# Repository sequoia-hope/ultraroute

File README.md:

# ultraroute

A KiCad autorouter under the MIT license, a benchmark that judges it by KiCad's own checks, and
**Studio**: a live, interactive view of the router at work. The project page is published at
<https://sequoia-hope.github.io/ultraroute/>; there the studio plays back recorded runs.

The router is the core in `core/`: Rust crates that read a `.kicad_pcb`, route it and write it
back, keeping every byte they did not change. It runs as a command, `ultraroute route`, and the
same code compiled to WebAssembly routes in the studio's browser tab. On the PCBench sample it
benchmarks on (200 boards, 120 s each), 164 boards come out clean by KiCad's DRC (see
`ROADMAP.md`, "State at 2026-10-30").

## Build and route a board

Needs Rust (`core/rust-toolchain.toml` pins 1.95.0). From `core/`:

```sh
cargo build --release -p ultraroute -p kicad-text
target/release/ultraroute route fixtures/earring.kicad_pcb -o /tmp/routed.kicad_pcb --timeout 120
```

With no stage named it runs the default recipe, the benchmark's. `kicad-text` (GPL, below) strokes
copper and mask text as KiCad does; without it text is a box round it, which can cover pads. The rules come from the
`.kicad_pro` and `.kicad_dru` beside the input; pours are left for KiCad to refill.
`core/README.md` lists the crates, the stages in their order, and every flag, and shows how to
judge the result with KiCad; `ultraroute route --help` prints the flags.
`docs/library.md` is for programs of your own built on the crates.

## Benchmark

`tools/pcbench.py` routes boards of [PCBench](https://github.com/emshotton/PCBench) from bare
pads and judges each by KiCad 9 (zone refill, then DRC). `docs/pcbench.md` says how to prepare
the boards, run a sample, and compare two runs against the noise floor.

## Run the studio

Needs Rust (with the `wasm32-unknown-unknown` target), `wasm-pack` and Node 22.

```sh
studio/build.sh
studio/target/release/studio-server --root . --port <port>
```

`build.sh` builds the server, the core's `ultraroute`, and the core as WebAssembly for the tab.
Then open `http://localhost:<port>/studio/`: pick a board, route it with the default recipe or
stages of your choice, watch it route, drag or nudge parts, lock them, and see where the board
is congested. On this machine the port comes from the project registry, and `./serve.sh` starts
the server.

A Boardroom project opens by its path: `/?project=<absolute path>&board=<name>&variant=<v>`
(board and variant may be left out when the project has one board). The studio routes
`hw/<board>/<variant>/<board>.kicad_pcb` with the `.kicad_pro`, `.kicad_dru` and `routing.json`
beside it; **Save to project** writes the routed board back over that file, unless it changed on
disk since it was loaded, and records the route and the router's report under
`apps.studio.<board>` in `design/status.json`.

| Path | What |
|---|---|
| `core/` | The router: crates, the `ultraroute` command, test fixtures |
| `studio/` | Server (runs the router, relays its live stream), Rust scene core compiled to WASM, Svelte client |
| `tools/pcbench.py`, `tools/lab.py` | The benchmark, and lab runs recorded under `~/Software/ultraroute-lab` |
| `docs/` | The library guide, the benchmark, the studio's design, research notes |
| `lab/` | Pages of recorded stage films and fan-out experiments |
| `ROADMAP.md` | The plan, phase by phase |

## Legacy: copperroute

Before the core, the router was [copperroute](https://github.com/sequoia-hope/copperroute) (branch
`governance`, forked from emshotton/copperroute), a Rust port of freerouting, run as a separate
program from a checkout at `copperroute/`. It is kept as a reference router. The studio can still
run it on the jobs that have a Specctra `.dsn` when its binary is at `target-
topo/release/copperroute` (or given with `--router PATH`); without it the studio routes on the core
alone. The tools of that era are kept under [`legacy/`](legacy/README.md): the leaderboard runner,
the two-router KiCad bench, the morph viewer and the experiment history. They are not maintained and
not on the Pages site. copperroute is GPL-3.0-only (a derivative of freerouting, with parts of
KiCad's design-rule checker); ultraroute does not include or link its code and runs it only as a
separate process.

## License

ultraroute is MIT-licensed; see [LICENSE](LICENSE). The core is our own code, written from the
file formats, so its WebAssembly build in the studio is MIT too. Code from GPL routers must stay
out of `core/` and `studio/`: linking it in, natively or as WebAssembly, would make the studio a
GPL work.

One crate is the exception, and it is a program, not a library: `core/crates/kicad-text` carries
KiCad's `newstroke` font and text layout, so it is GPL-3.0-or-later ([its LICENSE](core/crates/kicad-text/LICENSE)).
The reader runs it as a separate process (`kicad_pcb::text`), sending the board's texts on its
standard input and reading their strokes back; no MIT crate depends on it, which
`core/crates/kicad-pcb/tests/gpl_boundary.rs` checks over the whole dependency graph.

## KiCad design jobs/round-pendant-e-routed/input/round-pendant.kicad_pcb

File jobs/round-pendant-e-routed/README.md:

# round-pendant-e-routed

round-pendant's 8-layer variant E as released (github.com/sequoia-hope/round-pendant
`hw/round-pendant/e/round-pendant.*` at 2fcf971): a 38 mm round pendant, 235 XL-1010RGB LEDs on
a golden-angle spiral, five IS31FL3745 WLCSP-36 drivers, an RP2350A, 342 parts, 1218
connections, 5221 tracks and 879 vias. Every connection is joined: 0 DRC errors or warnings and
0 unconnected items by KiCad 9's DRC with `--severity-all`, as round-pendant reports.

It is a finished board to look at, not a routing job: the studio loads it as it is
(`strip: false`), and a route from it has nothing left to join. round-pendant routed it with
ultraroute in stages (`scripts/bga/critpass_d.py`, `escape_d.py`, `plough_finish_d.py`, then
`clean_copper_d.py`). One run from bare pads does not finish it yet: with its recipe
(`--strip --planes In2.Cu,In5.Cu --negotiate --rip-up --tighten --prefanout --prefanout-order inner
--prefanout-mode inner --diff-pairs --shove-plough region ... --cell 0.025`, 8 threads,
`--timeout 600`) the core at 24fb5d3 leaves 47 of 1042 connections open; with only `--strip` and
120 s, 104.

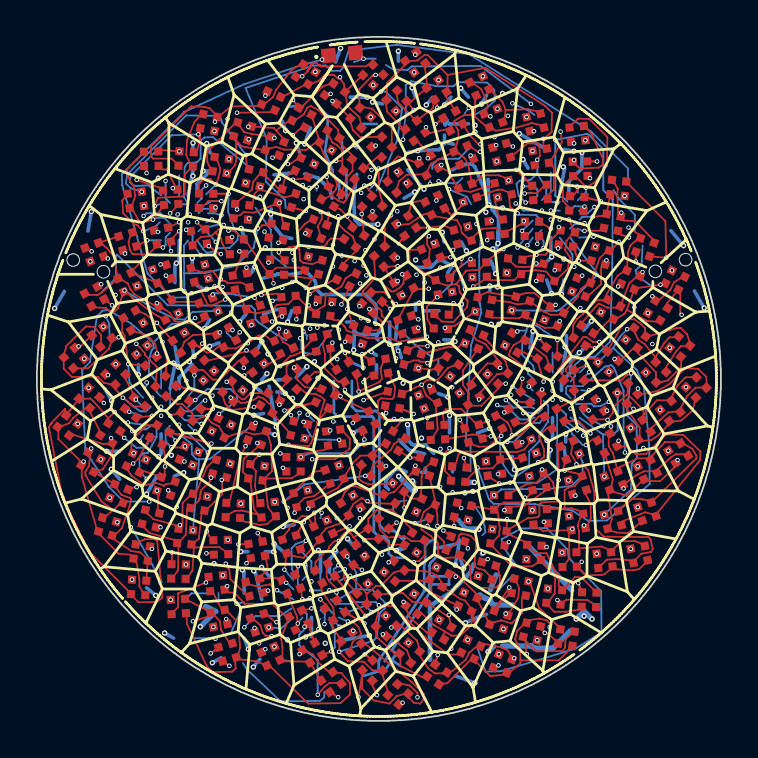
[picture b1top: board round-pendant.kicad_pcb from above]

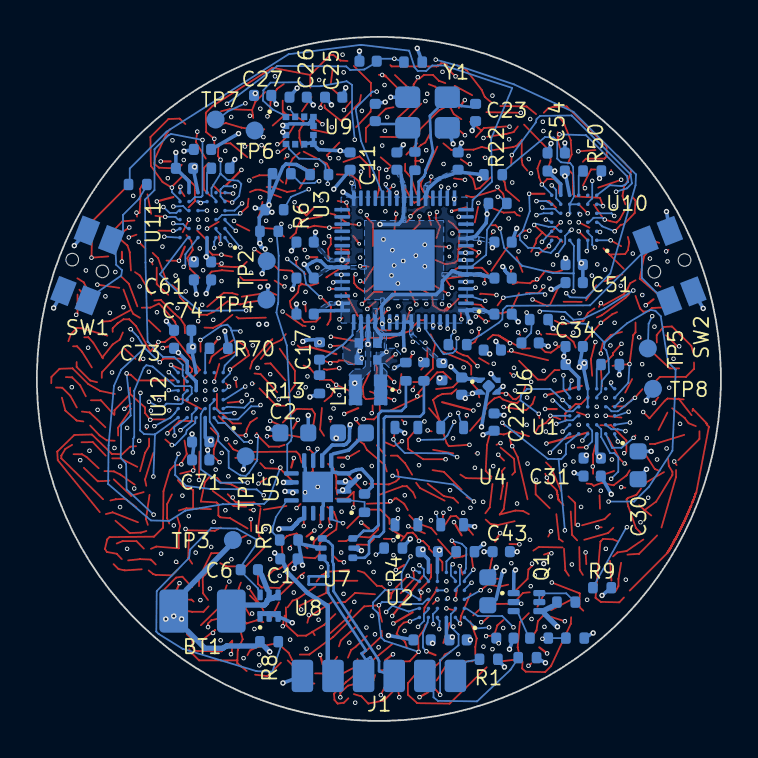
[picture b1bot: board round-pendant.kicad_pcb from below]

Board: 8 copper layers, 38.0 x 38.0 mm, 342 parts (106 on the bottom side), 185 nets.

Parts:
BT1: CELL 403535; BatteryPads
C1, C3, C4, C31, C34, C41, C44, C51, C54, C61, C64, C71, C74: 1u; C_0402_1005Metric
C2, C30, C40: 22u; C_0603_1608Metric
C5: 10u; C_0603_1608Metric
C6, C7, C8, C9, C10, C11, C12, C13, C14, C20, C21, C22, C25, C27, C32, C33, C35, C42, C43, C52, C53, C62, C63, C70, C72, C73: 100n; C_0402_1005Metric
C16, C18: 4.7u; C_0402_1005Metric_small_pads
C17, C19, C26: 4.7u; C_0402_1005Metric
C23, C24: 15p; C_0402_1005Metric
D1, D2, D3, D4, D5, D6, D7, D8, D9, D10, D11, D12, D13, D14, D15, D16, D17, D18, D19, D20, D21, D22, D23, D24, D25, D26, D27, D28, D29, D30, D31, D32, D33, D34, D35, D36, D37, D38, D39, D40, D41, D42, D43, D44, D45, D46, D47, D48, D49, D50, D51, D52, D53, D54, D55, D56, D57, D58, D59, D60, D61, D62, D63, D64, D65, D66, D67, D68, D69, D70, D71, D72, D73, D74, D75, D76, D77, D78, D79, D80, D81, D82, D83, D84, D85, D86, D87, D88, D89, D90, D91, D92, D93, D94, D95, D96, D97, D98, D99, D100, D101, D102, D103, D104, D105, D106, D107, D108, D109, D110, D111, D112, D113, D114, D115, D116, D117, D118, D119, D120, D121, D122, D123, D124, D125, D126, D127, D128, D129, D130, D131, D132, D133, D134, D135, D136, D137, D138, D139, D140, D141, D142, D143, D144, D145, D146, D147, D148, D149, D150, D151, D152, D153, D154, D155, D156, D157, D158, D159, D160, D161, D162, D163, D164, D165, D166, D167, D168, D169, D170, D171, D172, D173, D174, D175, D176, D177, D178, D179, D180, D181, D182, D183, D184, D185, D186, D187, D188, D189, D190, D191, D192, D193, D194, D195, D196, D197, D198, D199, D200, D201, D202, D203, D204, D205, D206, D207, D208, D209, D210, D211, D212, D213, D214, D215, D216, D217, D218, D219, D220, D221, D222, D223, D224, D225, D226, D227, D228, D229, D230, D231, D232, D233, D234, D235: RGB; LED_XL-1010RGB
J1: USB wires; USB_Pads
L1: 3.3u; L_pol_2016
Q1: NTZD3155C; SOT-563
Q2: ALS-PT19; SENSOR_ALS-PT19
R1, R2: 5.1k; R_0402_1005Metric
R3: 10k; R_0402_1005Metric
R4: 3k; R_0402_1005Metric
R5: 3.6k; R_0402_1005Metric
R6, R7, R9, R10, R11, R12, R31: 100k; R_0402_1005Metric
R8: 100R; R_0402_1005Metric
R13: 33R; R_0402_1005Metric
R14, R15: 27R; R_0402_1005Metric
R16, R17, R18, R21, R22: 1k; R_0402_1005Metric
R19, R20: 4.7k; R_0402_1005Metric
R30, R33, R50, R60, R70: 30k; R_0402_1005Metric
R43: 22k; R_0402_1005Metric
SW1: USER / WAKE; SW_Panasonic_EVQP7C
SW2: BOOTSEL; SW_Panasonic_EVQP7C
TP1: VSYS; TestPoint_Pad_D1.0mm
TP2: +3V3; TestPoint_Pad_D1.0mm
TP3: VBAT; TestPoint_Pad_D1.0mm
TP4: 1V1; TestPoint_Pad_D1.0mm
TP5: RUN; TestPoint_Pad_D1.0mm
TP6: SWCLK; TestPoint_Pad_D1.0mm
TP7: SWDIO; TestPoint_Pad_D1.0mm
TP8: GND; TestPoint_Pad_D1.0mm
U1, U2, U10, U11, U12: IS31FL3745; WLCSP-36_2.9x2.9mm_P0.5mm
U3: RP2350A; RP2350-QFN-60-1EP_7x7_P0.4mm_EP3.4x3.4mm_ThermalVias
U4: W25Q128JVPIQ; WSON-8_6x5mm_P1.27mm_NoEPCopper
U5: BQ24073; QFN-16-1EP_3x3mm_P0.5mm_EP1.7x1.7mm
U6: TPS7A0233; Texas_X2SON-4_1x1mm_P0.65mm
U7: USBLC6-2P6; SOT-666
U8: XB9901A; XySemi_DFN-6_1.8x1.4mm
U9: LIS2DW12; LGA-12_2x2mm_P0.5mm
Y1: 12MHz; Crystal_SMD_3225-4Pin_3.2x2.5mm

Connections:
+1V1: C18.1, C19.1, C20.1, C21.1, L1.1, TP4.1, U3.6, U3.23, U3.39, U3.50
+3V3: C4.1, C8.1, C9.1, C10.1, C11.1, C12.1, C13.1, C14.1, C16.1, C22.1, C25.1, C26.1, C27.1, R6.1, R7.1, R13.1, R19.1, R20.1, R21.1, R22.1, TP2.1, U3.1, U3.11, U3.20, U3.30, U3.38, U3.44, U3.45, U3.49, U3.53, U3.54, U4.8, U5.6, U6.1, U9.2, U9.3, U9.9, U9.10
/Driver 1 and matrix/CS1_1: D1.4, D2.4, D3.4, D4.4, D5.4, D6.4, D7.4, D8.4, U1.B2
/Driver 1 and matrix/CS1_2: D1.2, D2.2, D3.2, D4.2, D5.2, D6.2, D7.2, D8.2, U1.B3
/Driver 1 and matrix/CS1_3: D1.1, D2.1, D3.1, D4.1, D5.1, D6.1, D7.1, D8.1, U1.C3
/Driver 1 and matrix/CS1_4: D9.4, D10.4, D11.4, D12.4, D13.4, D14.4, D15.4, D16.4, U1.C2
/Driver 1 and matrix/CS1_5: D9.2, D10.2, D11.2, D12.2, D13.2, D14.2, D15.2, D16.2, U1.D2
/Driver 1 and matrix/CS1_6: D9.1, D10.1, D11.1, D12.1, D13.1, D14.1, D15.1, D16.1, U1.D1
/Driver 1 and matrix/CS1_7: D17.4, D18.4, D19.4, D20.4, D21.4, D22.4, D23.4, D24.4, U1.E2
/Driver 1 and matrix/CS1_8: D17.2, D18.2, D19.2, D20.2, D21.2, D22.2, D23.2, D24.2, U1.E1
/Driver 1 and matrix/CS1_9: D17.1, D18.1, D19.1, D20.1, D21.1, D22.1, D23.1, D24.1, U1.F1
/Driver 1 and matrix/CS1_10: D25.4, D26.4, D27.4, D28.4, D29.4, D30.4, D31.4, D32.4, U1.F6
/Driver 1 and matrix/CS1_11: D25.2, D26.2, D27.2, D28.2, D29.2, D30.2, D31.2, D32.2, U1.E6
/Driver 1 and matrix/CS1_12: D25.1, D26.1, D27.1, D28.1, D29.1, D30.1, D31.1, D32.1, U1.D5
/Driver 1 and matrix/CS1_13: D33.4, D34.4, D35.4, D36.4, D37.4, D38.4, D39.4, D40.4, U1.D6
/Driver 1 and matrix/CS1_14: D33.2, D34.2, D35.2, D36.2, D37.2, D38.2, D39.2, D40.2, U1.C4
/Driver 1 and matrix/CS1_15: D33.1, D34.1, D35.1, D36.1, D37.1, D38.1, D39.1, D40.1, U1.C6
/Driver 1 and matrix/CS1_16: D41.4, D42.4, D43.4, D44.4, D45.4, D46.4, D47.4, U1.C5
/Driver 1 and matrix/CS1_17: D41.2, D42.2, D43.2, D44.2, D45.2, D46.2, D47.2, U1.B4
/Driver 1 and matrix/CS1_18: D41.1, D42.1, D43.1, D44.1, D45.1, D46.1, D47.1, U1.B5
/Driver 1 and matrix/SW1_1: D1.3, D9.3, D17.3, D25.3, D33.3, D41.3, U1.A2
/Driver 1 and matrix/SW1_2: D2.3, D10.3, D18.3, D26.3, D34.3, D42.3, U1.A4
/Driver 1 and matrix/SW1_3: D3.3, D11.3, D19.3, D27.3, D35.3, D43.3, U1.A1
/Driver 1 and matrix/SW1_4: D4.3, D12.3, D20.3, D28.3, D36.3, D44.3, U1.A5
/Driver 1 and matrix/SW1_5: D5.3, D13.3, D21.3, D29.3, D37.3, D45.3, U1.B1
/Driver 1 and matrix/SW1_6: D6.3, D14.3, D22.3, D30.3, D38.3, D46.3, U1.A6
/Driver 1 and matrix/SW1_7: D7.3, D15.3, D23.3, D31.3, D39.3, D47.3, U1.C1
/Driver 1 and matrix/SW1_8: D8.3, D16.3, D24.3, D32.3, D40.3, U1.B6
/Driver 2 and matrix/CS2_1: D48.4, D49.4, D50.4, D51.4, D52.4, D53.4, D54.4, D55.4, U2.B2
/Driver 2 and matrix/CS2_2: D48.2, D49.2, D50.2, D51.2, D52.2, D53.2, D54.2, D55.2, U2.B3
/Driver 2 and matrix/CS2_3: D48.1, D49.1, D50.1, D51.1, D52.1, D53.1, D54.1, D55.1, U2.C3
/Driver 2 and matrix/CS2_4: D56.4, D57.4, D58.4, D59.4, D60.4, D61.4, D62.4, D63.4, U2.C2
/Driver 2 and matrix/CS2_5: D56.2, D57.2, D58.2, D59.2, D60.2, D61.2, D62.2, D63.2, U2.D2
/Driver 2 and matrix/CS2_6: D56.1, D57.1, D58.1, D59.1, D60.1, D61.1, D62.1, D63.1, U2.D1
/Driver 2 and matrix/CS2_7: D64.4, D65.4, D66.4, D67.4, D68.4, D69.4, D70.4, D71.4, U2.E2
/Driver 2 and matrix/CS2_8: D64.2, D65.2, D66.2, D67.2, D68.2, D69.2, D70.2, D71.2, U2.E1
/Driver 2 and matrix/CS2_9: D64.1, D65.1, D66.1, D67.1, D68.1, D69.1, D70.1, D71.1, U2.F1
/Driver 2 and matrix/CS2_10: D72.4, D73.4, D74.4, D75.4, D76.4, D77.4, D78.4, D79.4, U2.F6
/Driver 2 and matrix/CS2_11: D72.2, D73.2, D74.2, D75.2, D76.2, D77.2, D78.2, D79.2, U2.E6
/Driver 2 and matrix/CS2_12: D72.1, D73.1, D74.1, D75.1, D76.1, D77.1, D78.1, D79.1, U2.D5
/Driver 2 and matrix/CS2_13: D80.4, D81.4, D82.4, D83.4, D84.4, D85.4, D86.4, D87.4, U2.D6
/Driver 2 and matrix/CS2_14: D80.2, D81.2, D82.2, D83.2, D84.2, D85.2, D86.2, D87.2, U2.C4
/Driver 2 and matrix/CS2_15: D80.1, D81.1, D82.1, D83.1, D84.1, D85.1, D86.1, D87.1, U2.C6
/Driver 2 and matrix/CS2_16: D88.4, D89.4, D90.4, D91.4, D92.4, D93.4, D94.4, U2.C5
/Driver 2 and matrix/CS2_17: D88.2, D89.2, D90.2, D91.2, D92.2, D93.2, D94.2, U2.B4
/Driver 2 and matrix/CS2_18: D88.1, D89.1, D90.1, D91.1, D92.1, D93.1, D94.1, U2.B5
/Driver 2 and matrix/SW2_1: D48.3, D56.3, D64.3, D72.3, D80.3, D88.3, U2.A2
/Driver 2 and matrix/SW2_2: D49.3, D57.3, D65.3, D73.3, D81.3, D89.3, U2.A4
/Driver 2 and matrix/SW2_3: D50.3, D58.3, D66.3, D74.3, D82.3, D90.3, U2.A1
/Driver 2 and matrix/SW2_4: D51.3, D59.3, D67.3, D75.3, D83.3, D91.3, U2.A5
/Driver 2 and matrix/SW2_5: D52.3, D60.3, D68.3, D76.3, D84.3, D92.3, U2.B1
/Driver 2 and matrix/SW2_6: D53.3, D61.3, D69.3, D77.3, D85.3, D93.3, U2.A6
/Driver 2 and matrix/SW2_7: D54.3, D62.3, D70.3, D78.3, D86.3, D94.3, U2.C1
/Driver 2 and matrix/SW2_8: D55.3, D63.3, D71.3, D79.3, D87.3, U2.B6
/Driver 3 and matrix/CS3_1: D95.4, D96.4, D97.4, D98.4, D99.4, D100.4, D101.4, D102.4, U10.B2
/Driver 3 and matrix/CS3_2: D95.2, D96.2, D97.2, D98.2, D99.2, D100.2, D101.2, D102.2, U10.B3
/Driver 3 and matrix/CS3_3: D95.1, D96.1, D97.1, D98.1, D99.1, D100.1, D101.1, D102.1, U10.C3
/Driver 3 and matrix/CS3_4: D103.4, D104.4, D105.4, D106.4, D107.4, D108.4, D109.4, D110.4, U10.C2
/Driver 3 and matrix/CS3_5: D103.2, D104.2, D105.2, D106.2, D107.2, D108.2, D109.2, D110.2, U10.D2
/Driver 3 and matrix/CS3_6: D103.1, D104.1, D105.1, D106.1, D107.1, D108.1, D109.1, D110.1, U10.D1
/Driver 3 and matrix/CS3_7: D111.4, D112.4, D113.4, D114.4, D115.4, D116.4, D117.4, D118.4, U10.E2
/Driver 3 and matrix/CS3_8: D111.2, D112.2, D113.2, D114.2, D115.2, D116.2, D117.2, D118.2, U10.E1
/Driver 3 and matrix/CS3_9: D111.1, D112.1, D113.1, D114.1, D115.1, D116.1, D117.1, D118.1, U10.F1
/Driver 3 and matrix/CS3_10: D119.4, D120.4, D121.4, D122.4, D123.4, D124.4, D125.4, D126.4, U10.F6
/Driver 3 and matrix/CS3_11: D119.2, D120.2, D121.2, D122.2, D123.2, D124.2, D125.2, D126.2, U10.E6
/Driver 3 and matrix/CS3_12: D119.1, D120.1, D121.1, D122.1, D123.1, D124.1, D125.1, D126.1, U10.D5
/Driver 3 and matrix/CS3_13: D127.4, D128.4, D129.4, D130.4, D131.4, D132.4, D133.4, D134.4, U10.D6
/Driver 3 and matrix/CS3_14: D127.2, D128.2, D129.2, D130.2, D131.2, D132.2, D133.2, D134.2, U10.C4
/Driver 3 and matrix/CS3_15: D127.1, D128.1, D129.1, D130.1, D131.1, D132.1, D133.1, D134.1, U10.C6
/Driver 3 and matrix/CS3_16: D135.4, D136.4, D137.4, D138.4, D139.4, D140.4, D141.4, U10.C5
/Driver 3 and matrix/CS3_17: D135.2, D136.2, D137.2, D138.2, D139.2, D140.2, D141.2, U10.B4
/Driver 3 and matrix/CS3_18: D135.1, D136.1, D137.1, D138.1, D139.1, D140.1, D141.1, U10.B5
/Driver 3 and matrix/SW3_1: D95.3, D103.3, D111.3, D119.3, D127.3, D135.3, U10.A2
/Driver 3 and matrix/SW3_2: D96.3, D104.3, D112.3, D120.3, D128.3, D136.3, U10.A4
/Driver 3 and matrix/SW3_3: D97.3, D105.3, D113.3, D121.3, D129.3, D137.3, U10.A1
/Driver 3 and matrix/SW3_4: D98.3, D106.3, D114.3, D122.3, D130.3, D138.3, U10.A5
/Driver 3 and matrix/SW3_5: D99.3, D107.3, D115.3, D123.3, D131.3, D139.3, U10.B1
/Driver 3 and matrix/SW3_6: D100.3, D108.3, D116.3, D124.3, D132.3, D140.3, U10.A6
/Driver 3 and matrix/SW3_7: D101.3, D109.3, D117.3, D125.3, D133.3, D141.3, U10.C1
/Driver 3 and matrix/SW3_8: D102.3, D110.3, D118.3, D126.3, D134.3, U10.B6
/Driver 4 and matrix/CS4_1: D142.4, D143.4, D144.4, D145.4, D146.4, D147.4, D148.4, D149.4, U11.B2
/Driver 4 and matrix/CS4_2: D142.2, D143.2, D144.2, D145.2, D146.2, D147.2, D148.2, D149.2, U11.B3
/Driver 4 and matrix/CS4_3: D142.1, D143.1, D144.1, D145.1, D146.1, D147.1, D148.1, D149.1, U11.C3
/Driver 4 and matrix/CS4_4: D150.4, D151.4, D152.4, D153.4, D154.4, D155.4, D156.4, D157.4, U11.C2
/Driver 4 and matrix/CS4_5: D150.2, D151.2, D152.2, D153.2, D154.2, D155.2, D156.2, D157.2, U11.D2
/Driver 4 and matrix/CS4_6: D150.1, D151.1, D152.1, D153.1, D154.1, D155.1, D156.1, D157.1, U11.D1
/Driver 4 and matrix/CS4_7: D158.4, D159.4, D160.4, D161.4, D162.4, D163.4, D164.4, D165.4, U11.E2
/Driver 4 and matrix/CS4_8: D158.2, D159.2, D160.2, D161.2, D162.2, D163.2, D164.2, D165.2, U11.E1
/Driver 4 and matrix/CS4_9: D158.1, D159.1, D160.1, D161.1, D162.1, D163.1, D164.1, D165.1, U11.F1
/Driver 4 and matrix/CS4_10: D166.4, D167.4, D168.4, D169.4, D170.4, D171.4, D172.4, D173.4, U11.F6
/Driver 4 and matrix/CS4_11: D166.2, D167.2, D168.2, D169.2, D170.2, D171.2, D172.2, D173.2, U11.E6
/Driver 4 and matrix/CS4_12: D166.1, D167.1, D168.1, D169.1, D170.1, D171.1, D172.1, D173.1, U11.D5
/Driver 4 and matrix/CS4_13: D174.4, D175.4, D176.4, D177.4, D178.4, D179.4, D180.4, D181.4, U11.D6
/Driver 4 and matrix/CS4_14: D174.2, D175.2, D176.2, D177.2, D178.2, D179.2, D180.2, D181.2, U11.C4
/Driver 4 and matrix/CS4_15: D174.1, D175.1, D176.1, D177.1, D178.1, D179.1, D180.1, D181.1, U11.C6
/Driver 4 and matrix/CS4_16: D182.4, D183.4, D184.4, D185.4, D186.4, D187.4, D188.4, U11.C5
/Driver 4 and matrix/CS4_17: D182.2, D183.2, D184.2, D185.2, D186.2, D187.2, D188.2, U11.B4
/Driver 4 and matrix/CS4_18: D182.1, D183.1, D184.1, D185.1, D186.1, D187.1, D188.1, U11.B5
/Driver 4 and matrix/SW4_1: D142.3, D150.3, D158.3, D166.3, D174.3, D182.3, U11.A2
/Driver 4 and matrix/SW4_2: D143.3, D151.3, D159.3, D167.3, D175.3, D183.3, U11.A4
/Driver 4 and matrix/SW4_3: D144.3, D152.3, D160.3, D168.3, D176.3, D184.3, U11.A1
/Driver 4 and matrix/SW4_4: D145.3, D153.3, D161.3, D169.3, D177.3, D185.3, U11.A5
/Driver 4 and matrix/SW4_5: D146.3, D154.3, D162.3, D170.3, D178.3, D186.3, U11.B1
/Driver 4 and matrix/SW4_6: D147.3, D155.3, D163.3, D171.3, D179.3, D187.3, U11.A6
/Driver 4 and matrix/SW4_7: D148.3, D156.3, D164.3, D172.3, D180.3, D188.3, U11.C1
/Driver 4 and matrix/SW4_8: D149.3, D157.3, D165.3, D173.3, D181.3, U11.B6
/Driver 5 and matrix/CS5_1: D189.4, D190.4, D191.4, D192.4, D193.4, D194.4, D195.4, D196.4, U12.B2
/Driver 5 and matrix/CS5_2: D189.2, D190.2, D191.2, D192.2, D193.2, D194.2, D195.2, D196.2, U12.B3
/Driver 5 and matrix/CS5_3: D189.1, D190.1, D191.1, D192.1, D193.1, D194.1, D195.1, D196.1, U12.C3
/Driver 5 and matrix/CS5_4: D197.4, D198.4, D199.4, D200.4, D201.4, D202.4, D203.4, D204.4, U12.C2
/Driver 5 and matrix/CS5_5: D197.2, D198.2, D199.2, D200.2, D201.2, D202.2, D203.2, D204.2, U12.D2
/Driver 5 and matrix/CS5_6: D197.1, D198.1, D199.1, D200.1, D201.1, D202.1, D203.1, D204.1, U12.D1
/Driver 5 and matrix/CS5_7: D205.4, D206.4, D207.4, D208.4, D209.4, D210.4, D211.4, D212.4, U12.E2
/Driver 5 and matrix/CS5_8: D205.2, D206.2, D207.2, D208.2, D209.2, D210.2, D211.2, D212.2, U12.E1
/Driver 5 and matrix/CS5_9: D205.1, D206.1, D207.1, D208.1, D209.1, D210.1, D211.1, D212.1, U12.F1
/Driver 5 and matrix/CS5_10: D213.4, D214.4, D215.4, D216.4, D217.4, D218.4, D219.4, D220.4, U12.F6
/Driver 5 and matrix/CS5_11: D213.2, D214.2, D215.2, D216.2, D217.2, D218.2, D219.2, D220.2, U12.E6
/Driver 5 and matrix/CS5_12: D213.1, D214.1, D215.1, D216.1, D217.1, D218.1, D219.1, D220.1, U12.D5
/Driver 5 and matrix/CS5_13: D221.4, D222.4, D223.4, D224.4, D225.4, D226.4, D227.4, D228.4, U12.D6
/Driver 5 and matrix/CS5_14: D221.2, D222.2, D223.2, D224.2, D225.2, D226.2, D227.2, D228.2, U12.C4
/Driver 5 and matrix/CS5_15: D221.1, D222.1, D223.1, D224.1, D225.1, D226.1, D227.1, D228.1, U12.C6
/Driver 5 and matrix/CS5_16: D229.4, D230.4, D231.4, D232.4, D233.4, D234.4, D235.4, U12.C5
/Driver 5 and matrix/CS5_17: D229.2, D230.2, D231.2, D232.2, D233.2, D234.2, D235.2, U12.B4
/Driver 5 and matrix/CS5_18: D229.1, D230.1, D231.1, D232.1, D233.1, D234.1, D235.1, U12.B5
/Driver 5 and matrix/SW5_1: D189.3, D197.3, D205.3, D213.3, D221.3, D229.3, U12.A2
/Driver 5 and matrix/SW5_2: D190.3, D198.3, D206.3, D214.3, D222.3, D230.3, U12.A4
/Driver 5 and matrix/SW5_3: D191.3, D199.3, D207.3, D215.3, D223.3, D231.3, U12.A1
/Driver 5 and matrix/SW5_4: D192.3, D200.3, D208.3, D216.3, D224.3, D232.3, U12.A5
/Driver 5 and matrix/SW5_5: D193.3, D201.3, D209.3, D217.3, D225.3, D233.3, U12.B1
/Driver 5 and matrix/SW5_6: D194.3, D202.3, D210.3, D218.3, D226.3, D234.3, U12.A6
/Driver 5 and matrix/SW5_7: D195.3, D203.3, D211.3, D219.3, D227.3, D235.3, U12.C1
/Driver 5 and matrix/SW5_8: D196.3, D204.3, D212.3, D220.3, D228.3, U12.B6
/MCU/ACC_INT: U3.14, U9.12
/MCU/ACC_SCL: R19.2, U3.5, U9.1
/MCU/ACC_SDA: R20.2, U3.4, U9.4
/MCU/BTN: R18.1, U3.15
/MCU/LIGHT: C70.1, Q2.2, R43.1, U3.41
/MCU/LIGHT_PWR: Q2.1, U3.3
/MCU/QSPI_SCLK: U3.56, U4.6
/MCU/QSPI_SD0: U3.57, U4.5
/MCU/QSPI_SD1: U3.59, U4.2
/MCU/QSPI_SD2: U3.58, U4.3
/MCU/QSPI_SD3: U3.55, U4.7
/MCU/QSPI_SS: R16.1, U3.60, U4.1
/MCU/RUN: TP5.1, U3.26
/MCU/SWCLK: TP6.1, U3.24
/MCU/SWDIO: TP7.1, U3.25
/MCU/USB_DM_MCU: R14.2, U3.51
/MCU/USB_DP_MCU: R15.2, U3.52
/MCU/VREG_AVDD: C17.1, R13.2, U3.46
/MCU/VREG_LX: L1.2, U3.48
/Power/BAT_N: BT1.2, C6.2, U8.4, U8.5
/Power/CC1: J1.1, R1.1
/Power/CC2: J1.2, R2.1
/Power/USB_DM_C: J1.3, U7.1
/Power/USB_DP_C: J1.4, U7.3
CHG: R7.2, U3.16, U5.9
GND: C1.2, C2.2, C3.2, C4.2, C5.2, C7.2, C8.2, C9.2, C10.2, C11.2, C12.2, C13.2, C14.2, C16.2, C17.2, C18.2, C19.2, C20.2, C21.2, C22.2, C23.2, C24.2, C25.2, C26.2, C27.2, C30.2, C31.2, C32.2, C33.2, C34.2, C35.2, C40.2, C41.2, C42.2, C43.2, C44.2, C51.2, C52.2, C53.2, C54.2, C61.2, C62.2, C63.2, C64.2, C70.2, C71.2, C72.2, C73.2, C74.2, J1.6, Q1.1, R1.2, R2.2, R3.2, R4.2, R5.2, R9.2, R12.2, R30.2, R31.2, R33.2, R43.2, R50.2, R60.2, R70.2, SW1.2, SW2.2, TP8.1, U1.D4, U1.E4, U1.F4, U2.E4, U2.F4, U3.47, U3.61, U4.4, U5.4, U5.5, U5.8, U5.15, U5.17, U6.2, U6.5, U7.2, U8.1, U8.2, U8.3, U9.6, U9.7, U9.8, U10.F4, U11.F4, U12.F4, Y1.2, Y1.4
I2C_SCL: R22.2, U1.E3, U2.E3, U3.8, U10.D4, U10.E3, U10.E4, U11.E3, U11.E4, U12.E3
I2C_SDA: R21.2, U1.D3, U2.D3, U2.D4, U3.7, U10.D3, U11.D3, U11.D4, U12.D3
LED_SDB: C35.1, R31.1, U1.E5, U2.E5, U3.9, U10.E5, U11.E5, U12.E5
unnamed: C24.1, R17.1, Y1.3
unnamed: Q1.5, Q1.6, R10.2
unnamed: Q1.3, R11.1
unnamed: R16.2, SW2.1
unnamed: R18.2, SW1.1
unnamed: R30.1, U1.F3
unnamed: R33.1, U2.F3
unnamed: C23.1, U3.21, Y1.1
unnamed: R17.2, U3.22
unnamed: R5.1, U5.12
unnamed: R4.1, U5.16
unnamed: R3.1, U5.1
unnamed: C6.1, R8.2, U8.6
unnamed: R50.1, U10.F3
unnamed: R60.1, U11.F3
unnamed: R70.1, U12.F3
PGOOD: R6.2, U3.17, U5.7
USB_DM: R14.1, U7.6
USB_DP: R15.1, U7.4
VBAT: BT1.1, C5.1, Q1.4, R8.1, R10.1, TP3.1, U5.2, U5.3
VBAT_EN: Q1.2, R9.1, U3.18
VBAT_SENSE: C7.1, R11.2, R12.1, U3.40
VBUS: C1.1, J1.5, U5.13, U7.5
VSYS: C2.1, C3.1, C30.1, C31.1, C32.1, C33.1, C34.1, C40.1, C41.1, C42.1, C43.1, C44.1, C51.1, C52.1, C53.1, C54.1, C61.1, C62.1, C63.1, C64.1, C71.1, C72.1, C73.1, C74.1, TP1.1, U1.A3, U1.F5, U2.A3, U2.F5, U5.10, U5.11, U6.3, U6.4, U10.A3, U10.F5, U11.A3, U11.F5, U12.A3, U12.D4, U12.E4, U12.F5

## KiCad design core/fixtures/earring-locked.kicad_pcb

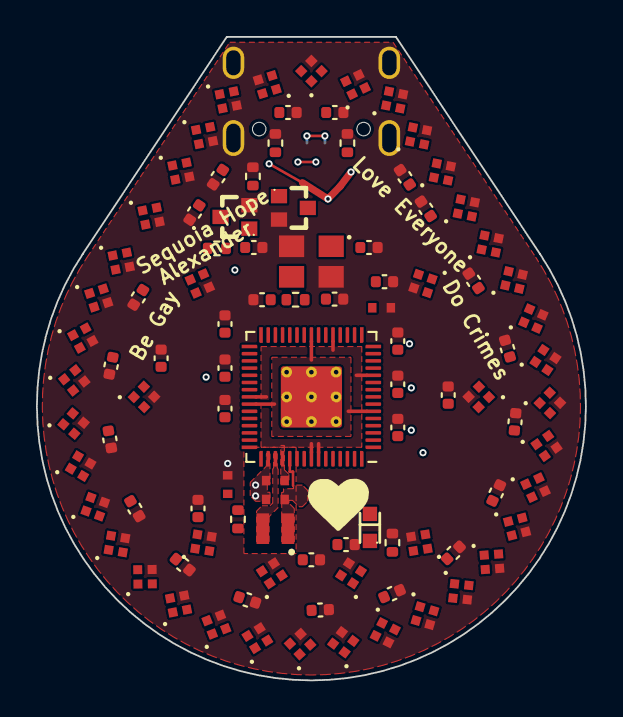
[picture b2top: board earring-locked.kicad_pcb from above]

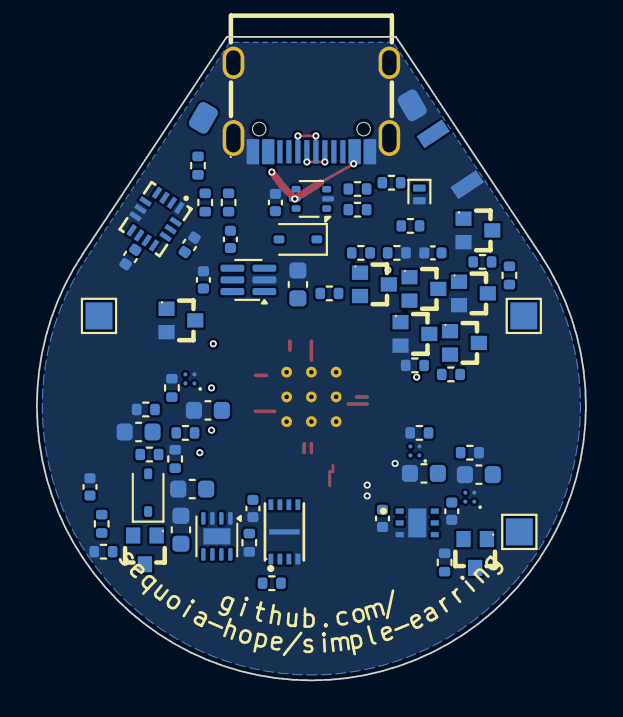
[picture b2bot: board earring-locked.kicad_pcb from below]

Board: 4 copper layers, 30.5 x 35.8 mm, 167 parts (70 on the bottom side), 103 nets.

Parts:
BT1: LPR302823; BAT_LPR302823_PADS
C1, C2, C3, C4, C5, C6, C7, C8, C9, C21, C23, C24, C25, C26, C27, C28, C30, C32, C34, C36, C38, C40, C42, C44, C46, C48, C50, C52, C54, C56, C58, C60, C62, C64, C66, C68, C70, C72, C74, C77: 100n; C_0402_1005Metric
C11, C12, C13, C22: 4.7u; C_0402_1005Metric_small_pads
C14, C15: 15p; C_0402_1005Metric
C16, C17, C20, C29, C75, C78, C79: 10u; C_0603_1608Metric
C18, C19: 1u; C_0402_1005Metric
C76: 10n; C_0402_1005Metric
D2: BAV99W; SOT-323_BAT54SW
D3: 1N4007WS; D_SOD-323
D4: BAV70W; SOT-323_BAT54SW
D5: 1N4148WS; D_SOD-323
D6: PESD5V0S1BL; D_SOD-882
J1: USB-C; USB-C_SMD-TYPE-C-31-M-12_1
L1: 3.3uH; L_pol_2016
LED1, LED2, LED3, LED4, LED5, LED6, LED7, LED8, LED9, LED10, LED11, LED12, LED13, LED14, LED15, LED16, LED17, LED18, LED19, LED20, LED21, LED22, LED23, LED24, LED25, LED26, LED27, LED28, LED29, LED30, LED31, LED32, LED33, LED34, LED35, LED36, LED37, LED38, LED39, LED40, LED41, LED42, LED43, LED44, LED45: WS2816C-1313; LED_WS2816C-1313
Q1: ALS-PT19; SENSOR_ALS-PT19
Q2, Q8: CJ2101; SOT-323_MOSFET
Q3, Q5, Q6, Q7, Q9, Q10: BSS138W; SOT-323_MOSFET
Q4: LBSS84WT1G; SOT-323_MOSFET
R1, R3, R23, R30, R31, R32: 1k; R_0402_1005Metric
R2, R10, R19, R20, R22, R33, R34: 10k; R_0402_1005Metric
R4, R5: 5.1k; R_0402_1005Metric
R6, R7: 27; R_0402_1005Metric
R8: 18k; R_0402_1005Metric
R11, R12, R21, R29: 1M; R_0402_1005Metric
R13: 33; R_0402_1005Metric
R14, R15, R27: 4.7k; R_0402_1005Metric
R16: 22k; R_0402_1005Metric
R17, R18, R24, R25, R26: 100k; R_0402_1005Metric
R28: 680k; R_0402_1005Metric
SW2: PWR; SW_B3U-3000P
TP1: RUN; TestPoint_Pad_1.5x1.5mm
TP2: SWCLK; TestPoint_Pad_1.5x1.5mm
TP3: SWDIO; TestPoint_Pad_1.5x1.5mm
U1: RP2350A; RP2350-QFN-60-1EP_7x7_P0.4mm_EP3.4x3.4mm_ThermalVias
U2: LGS4056H; DFN-8-1EP_2x2mm_P0.5mm_EP0.9x1.5mm
U3: NCP730-3.3; WDFN-6-2x2
U4, U9, U10: TPS22913; YZV0004ADAD
U5: USBLC6-2P6; SOT-666
U6: LSM6DS3TR-C; LGA-14_L3.0-W2.5-P0.50-TL
U7: W25Q16JVUXIQ; USON-8_L3.0-W2.0-P0.50-BL-EP
U8: 74LVC2G14; SOT-363_SC-70-6
Y1: 12MHz; Crystal_SMD_3225-4Pin_3.2x2.5mm_ABM8

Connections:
3V3: C1.1, C2.1, C3.1, C4.1, C7.1, C8.1, C9.1, C11.1, C19.1, C23.1, C24.1, C25.1, C77.1, Q1.1, Q8.2, R2.2, R13.1, R14.2, R15.2, R26.1, U1.1, U1.11, U1.20, U1.30, U1.38, U1.44, U1.45, U1.49, U1.53, U1.54, U3.1, U6.2, U6.3, U6.5, U6.8, U6.12, U7.8, U8.5
BOOTSEL: R3.1, U1.60, U7.1
BOOTSEL_SW: Q7.3, R3.2
BOOT_TMR: C75.1, D5.2, R28.2, U8.1
BTN_EXT: D6.1, R30.1, SW2.2
BTN_N: C27.1, D4.3, R30.2
BTN_SENSE: D5.1, Q8.3, R27.1, R28.1, U1.33
CC1: J1.A5, R4.1
CC2: J1.B5, R5.1
CHRG: U1.31, U2.7
CHRG_DONE: U1.42, U2.6
GND: BT1.2, C1.2, C2.2, C3.2, C4.2, C5.2, C6.2, C7.2, C8.2, C9.2, C11.2, C12.2, C13.2, C14.2, C15.2, C16.2, C17.2, C18.2, C19.2, C20.2, C21.2, C22.2, C23.2, C24.2, C25.2, C26.2, C27.2, C28.2, C29.2, C30.2, C32.2, C34.2, C36.2, C38.2, C40.2, C42.2, C44.2, C46.2, C48.2, C50.2, C52.2, C54.2, C56.2, C58.2, C60.2, C62.2, C64.2, C66.2, C68.2, C70.2, C72.2, C74.2, C75.2, C77.2, C78.2, C79.2, D6.2, J1.1, J1.2, J1.3, J1.4, J1.A1B12, J1.B1A12, LED1.3, LED2.3, LED3.3, LED4.3, LED5.3, LED6.3, LED7.3, LED8.3, LED9.3, LED10.3, LED11.3, LED12.3, LED13.3, LED14.3, LED15.3, LED16.3, LED17.3, LED18.3, LED19.3, LED20.3, LED21.3, LED22.3, LED23.3, LED24.3, LED25.3, LED26.3, LED27.3, LED28.3, LED29.3, LED30.3, LED31.3, LED32.3, LED33.3, LED34.3, LED35.3, LED36.3, LED37.3, LED38.3, LED39.3, LED40.3, LED41.3, LED42.3, LED43.3, LED44.3, LED45.3, Q3.2, Q5.2, Q6.2, Q7.2, Q9.2, Q10.2, R4.2, R5.2, R8.2, R10.2, R12.2, R16.2, R17.2, R20.2, R21.2, R25.2, R27.2, R29.2, R33.2, R34.2, SW2.1, U1.47, U1.61, U2.1, U2.3, U2.9, U3.3, U3.EP, U4.B1, U5.2, U6.1, U6.6, U6.7, U7.4, U7.9, U8.2, U9.B1, U10.B1, Y1.2, Y1.4
IMU_INT1: U1.12, U6.4
IMU_SCL: R15.1, U1.15, U6.13
IMU_SDA: R14.1, U1.9, U6.14
LATCH_G: D4.2, Q4.1, Q5.3, R24.2
LEDC_D0: LED38.4, Q10.3, R32.2
LEDC_D1: LED38.2, LED39.4
LEDC_D2: LED39.2, LED40.4
LEDC_D3: LED40.2, LED41.4
LEDC_D4: LED41.2, LED42.4
LEDC_D5: LED42.2, LED43.4
LEDC_D6: LED43.2, LED44.4
LEDC_D7: LED44.2, LED45.4
LEDL_D0: LED1.4, Q3.3, R23.2
LEDL_D1: LED1.2, LED2.4
LEDL_D2: LED2.2, LED3.4
LEDL_D3: LED3.2, LED4.4
LEDL_D4: LED4.2, LED5.4
LEDL_D5: LED5.2, LED6.4
LEDL_D6: LED6.2, LED7.4
LEDL_D7: LED7.2, LED8.4
LEDL_D8: LED8.2, LED9.4
LEDL_D9: LED9.2, LED10.4
LEDL_D10: LED10.2, LED11.4
LEDL_D11: LED11.2, LED12.4
LEDL_D12: LED12.2, LED13.4
LEDL_D13: LED13.2, LED14.4
LEDL_D14: LED14.2, LED15.4
LEDL_D15: LED15.2, LED16.4
LEDL_D16: LED16.2, LED17.4
LEDL_D17: LED17.2, LED18.4
LEDR_D0: LED37.4, Q9.3, R31.2
LEDR_D1: LED36.4, LED37.2
LEDR_D2: LED35.4, LED36.2
LEDR_D3: LED34.4, LED35.2
LEDR_D4: LED33.4, LED34.2
LEDR_D5: LED32.4, LED33.2
LEDR_D6: LED31.4, LED32.2
LEDR_D7: LED30.4, LED31.2
LEDR_D8: LED29.4, LED30.2
LEDR_D9: LED28.4, LED29.2
LEDR_D10: LED27.4, LED28.2
LEDR_D11: LED26.4, LED27.2
LEDR_D12: LED25.4, LED26.2
LEDR_D13: LED24.4, LED25.2
LEDR_D14: LED23.4, LED24.2
LEDR_D15: LED22.4, LED23.2
LEDR_D16: LED21.4, LED22.2
LEDR_D17: LED20.4, LED21.2
LEDR_D18: LED19.4, LED20.2
LED_DATA_C: Q10.1, U1.27
LED_DATA_L: Q3.1, U1.29
LED_DATA_R: Q9.1, U1.28
LED_EN_C: R34.1, U1.34, U10.B2
LED_EN_L: R10.1, U1.3, U4.B2
LED_EN_R: R33.1, U1.2, U9.B2
LIGHT: C26.1, Q1.2, R16.1, U1.40
LONG: C76.1, Q7.1, U8.4
LONG_N: U8.3, U8.6
PATH_GATE: Q2.1, R21.1, R22.2
PRESS_N: D4.1, Q8.1, R26.2
PROG: R8.1, U2.2
PWR_EN: D2.3, R17.1, R18.2, U3.4
PWR_HOLD: Q5.1, R25.1, U1.32
QSPI_SCLK: U1.56, U7.6
QSPI_SD0: U1.57, U7.5
QSPI_SD1: U1.59, U7.2
QSPI_SD2: U1.58, U7.3
QSPI_SD3: U1.55, U7.7
RUN: Q6.3, R2.1, TP1.1, U1.26
RUN_KICK: C76.2, Q6.1, R29.1
SWCLK: TP2.1, U1.24
SWDIO: TP3.1, U1.25
SW_ON: D2.1, Q4.3, R11.1
USB_C_DN: J1.A7, J1.B7, R7.1, U5.3, U5.4
USB_C_DP: J1.A6, J1.B6, R6.1, U5.1, U5.6
USB_DM: R7.2, U1.51
USB_DP: R6.2, U1.52
VBATT: BT1.1, C17.1, D2.2, Q2.3, Q4.2, R24.1, U2.5
VBSENSE: C21.1, R11.2, R12.1, U1.43
VBUS: C16.1, C28.1, D3.2, J1.A4B9, J1.B4A9, R18.1, R19.1, R22.1, U2.4, U2.8, U5.5
VBUS_SENSE: R19.2, R20.1, U1.41
VDD_CORE: C5.1, C6.1, C12.1, C13.1, L1.1, U1.6, U1.23, U1.39, U1.50
VLED_C: C68.1, C70.1, C72.1, C74.1, C79.1, LED38.1, LED39.1, LED40.1, LED41.1, LED42.1, LED43.1, LED44.1, LED45.1, R32.1, U10.A1
VLED_L: C20.1, C30.1, C32.1, C34.1, C36.1, C38.1, C40.1, C42.1, C44.1, C46.1, LED1.1, LED2.1, LED3.1, LED4.1, LED5.1, LED6.1, LED7.1, LED8.1, LED9.1, LED10.1, LED11.1, LED12.1, LED13.1, LED14.1, LED15.1, LED16.1, LED17.1, LED18.1, R23.1, U4.A1
VLED_R: C48.1, C50.1, C52.1, C54.1, C56.1, C58.1, C60.1, C62.1, C64.1, C66.1, C78.1, LED19.1, LED20.1, LED21.1, LED22.1, LED23.1, LED24.1, LED25.1, LED26.1, LED27.1, LED28.1, LED29.1, LED30.1, LED31.1, LED32.1, LED33.1, LED34.1, LED35.1, LED36.1, LED37.1, R31.1, U9.A1
VREG_AVDD: C22.1, R13.2, U1.46
VREG_LX: L1.2, U1.48
VSYS: C18.1, C29.1, D3.1, Q2.2, U3.6, U4.A2, U9.A2, U10.A2
XIN: C14.1, U1.21, Y1.1
XOUT: R1.2, U1.22
XTAL_R: C15.1, R1.1, Y1.3

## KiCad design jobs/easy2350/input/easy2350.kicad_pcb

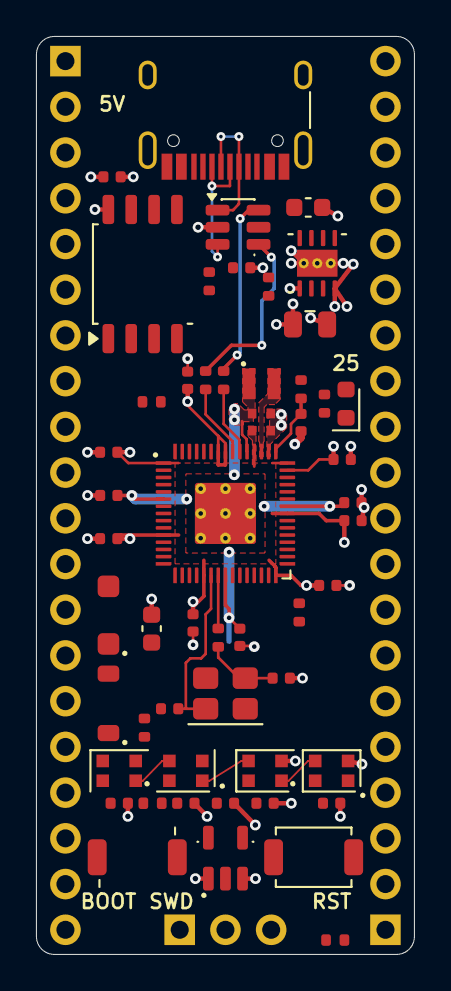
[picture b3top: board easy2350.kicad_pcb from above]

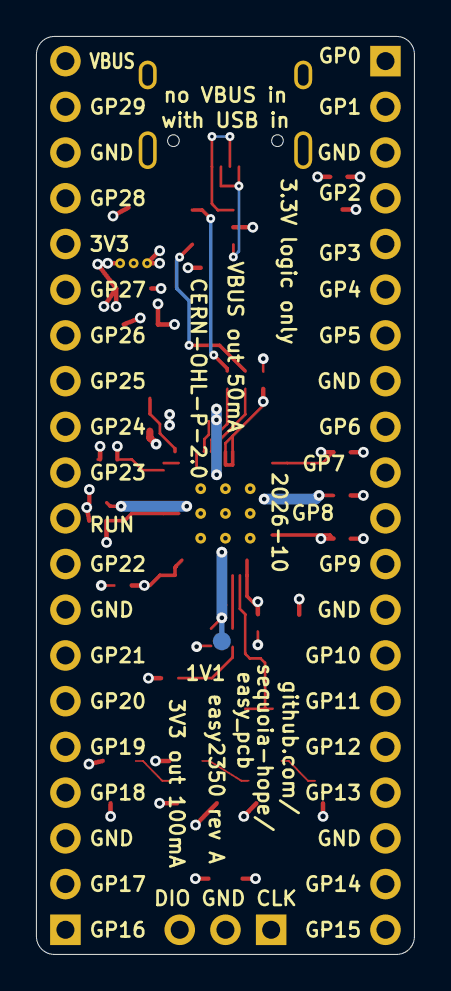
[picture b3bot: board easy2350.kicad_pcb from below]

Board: 4 copper layers, 21.0 x 51.0 mm, 58 parts (3 on the bottom side), 65 nets.

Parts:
C1, C4, C5, C6, C7, C8, C9, C11, C17, C18, C22, C24, C25, C26, C27, C28: 100n; C_0402_1005Metric
C2: 2.2u; C_0603_1608Metric
C3: 10u; C_0805_2012Metric
C13, C16: 4.7u; C_0402_1005Metric
C14, C15: 4.7u; C_0402_1005Metric_small_pads
C20, C21: 15p; C_0402_1005Metric
C23: 4.7u; C_0603_1608Metric
D1: RED; LED_0603_1608Metric
D2: SM4007PL; D_SOD-123F_MDD
D3, D4, D5, D6: WS2812B-2020-V6; LED_WS2812B-2020_PLCC4_2.0x2.0mm
D7: BZT52B5V1; D_SOD-123
J1: USB-C; USB_C_Receptacle_HRO_TYPE-C-31-M-12
J2: GPIO left; PinHeader_1x20_P2.54mm_Vertical
J3: GPIO right; PinHeader_1x20_P2.54mm_Vertical
J4: SWD; PinHeader_1x03_P2.54mm_Vertical
L1: 3.3u; L_pol_2016
R1, R2: 5.1k; R_0402_1005Metric
R3, R10: 33R; R_0402_1005Metric
R4, R5: 27R; R_0402_1005Metric
R6, R7, R8, R9: 1k; R_0402_1005Metric
R11: 4.7k; R_0402_1005Metric
R12: 100k; R_0402_1005Metric
SW1: BOOTSEL; SW_SPST_TS-1088-xR020
SW2: RESET; SW_SPST_TS-1088-xR020
TP3: 1V1; TestPoint_Pad_D1.0mm
U1: RP2350A; RP2350-QFN-60-1EP_7x7_P0.4mm_EP3.4x3.4mm_ThermalVias
U2: USBLC6-2SC6; SOT-23-6
U3: AP7361C-33FGE; DFN-8-1EP_3x3mm_P0.65mm_EP1.5x2.25mm_ThermalVias
U4: SN74LV1T125DBVR; SOT-23-5
U5: W25Q128JVSIQ; SOIC-8_5.3x5.3mm_P1.27mm
Y1: 12MHz; Crystal_SMD_3225-4Pin_3.2x2.5mm

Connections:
+1V1: C15.1, C16.1, C17.1, C18.1, L1.1, TP3.1, U1.6, U1.23, U1.39, U1.50
+3V3: C3.1, C4.1, C5.1, C6.1, C7.1, C8.1, C9.1, C11.1, C14.1, C22.1, J3.16, R3.1, U1.1, U1.11, U1.20, U1.30, U1.38, U1.44, U1.45, U1.49, U1.53, U1.54, U3.1, U5.8
/CC1: J1.A5, R1.1
/CC2: J1.B5, R2.1
/GPIO0: J2.1, U1.2
/GPIO1: J2.2, U1.3
/GPIO2: J2.4, U1.4
/GPIO3: J2.5, U1.5
/GPIO4: J2.6, U1.7
/GPIO5: J2.7, U1.8
/GPIO6: J2.9, U1.9
/GPIO7: J2.10, U1.10
/GPIO8: J2.11, U1.12
/GPIO9: J2.12, U1.13
/GPIO10: J2.14, U1.14
/GPIO11: J2.15, U1.15
/GPIO12: J2.16, U1.16
/GPIO13: J2.17, U1.17
/GPIO14: J2.19, U1.18
/GPIO15: J2.20, U1.19
/GPIO16: J3.1, U1.27
/GPIO17: J3.2, U1.28
/GPIO18: J3.4, U1.29
/GPIO19: J3.5, U1.31
/GPIO20: J3.6, U1.32
/GPIO21: J3.7, U1.33
/GPIO22: J3.9, U1.34
/GPIO23: J3.11, R12.1, U1.35, U4.2
/GPIO24: J3.12, U1.36
/GPIO25: J3.13, R9.1, U1.37
/GPIO26: J3.14, U1.40
/GPIO27: J3.15, U1.41
/GPIO28: J3.17, U1.42
/GPIO29: J3.19, U1.43
/LED_DIN: D3.3, R10.2
/PIX12: D3.1, D4.3
/PIX23: D4.1, D5.3
/PIX34: D5.1, D6.3
/QSPI_SCLK: U1.56, U5.6
/QSPI_SD0: U1.57, U5.5
/QSPI_SD1: U1.59, U5.2
/QSPI_SD2: U1.58, U5.3
/QSPI_SD3: U1.55, U5.7
/QSPI_SS: R7.1, U1.60, U5.1
/RUN: J3.10, R8.1, U1.26
/SWCLK: J4.1, U1.24
/SWDIO: J4.3, U1.25
/USB_DM: R4.1, U2.6
/USB_DM_C: J1.A7, J1.B7, U2.1
/USB_DM_MCU: R4.2, U1.51
/USB_DP: R5.1, U2.4
/USB_DP_C: J1.A6, J1.B6, U2.3
/USB_DP_MCU: R5.2, U1.52
/VREG_AVDD: C13.1, R3.2, U1.46
/VREG_LX: L1.2, U1.48
/XIN: C20.1, U1.21, Y1.1
/XOUT: R6.2, U1.22
/XOUT_R: C21.1, R6.1, Y1.3
GND: C1.2, C2.2, C3.2, C4.2, C5.2, C6.2, C7.2, C8.2, C9.2, C11.2, C13.2, C14.2, C15.2, C16.2, C17.2, C18.2, C20.2, C21.2, C22.2, C23.2, C24.2, C25.2, C26.2, C27.2, C28.2, D1.1, D3.2, D4.2, D5.2, D6.2, D7.2, J1.A1, J1.A12, J1.B1, J1.B12, J1.S1, J2.3, J2.8, J2.13, J2.18, J3.3, J3.8, J3.18, J4.2, R1.2, R2.2, R11.2, R12.2, SW1.1, SW2.1, U1.47, U1.61, U2.2, U3.4, U3.9, U4.1, U4.3, U5.4, Y1.2, Y1.4
unnamed: D1.2, R9.2
unnamed: R7.2, SW1.2
unnamed: R8.2, SW2.2
unnamed: R10.1, U4.4
VBUS: C1.1, C2.1, D2.2, J1.A4, J1.A9, J1.B4, J1.B9, J3.20, U2.5, U3.5, U3.8
VLED: C23.1, C24.1, C25.1, C26.1, C27.1, C28.1, D2.1, D3.4, D4.4, D5.4, D6.4, D7.1, R11.1, U4.5

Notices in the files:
jobs/easy2350/input/easy2350.kicad_pcb:
CERN-OHL-P-2.0
